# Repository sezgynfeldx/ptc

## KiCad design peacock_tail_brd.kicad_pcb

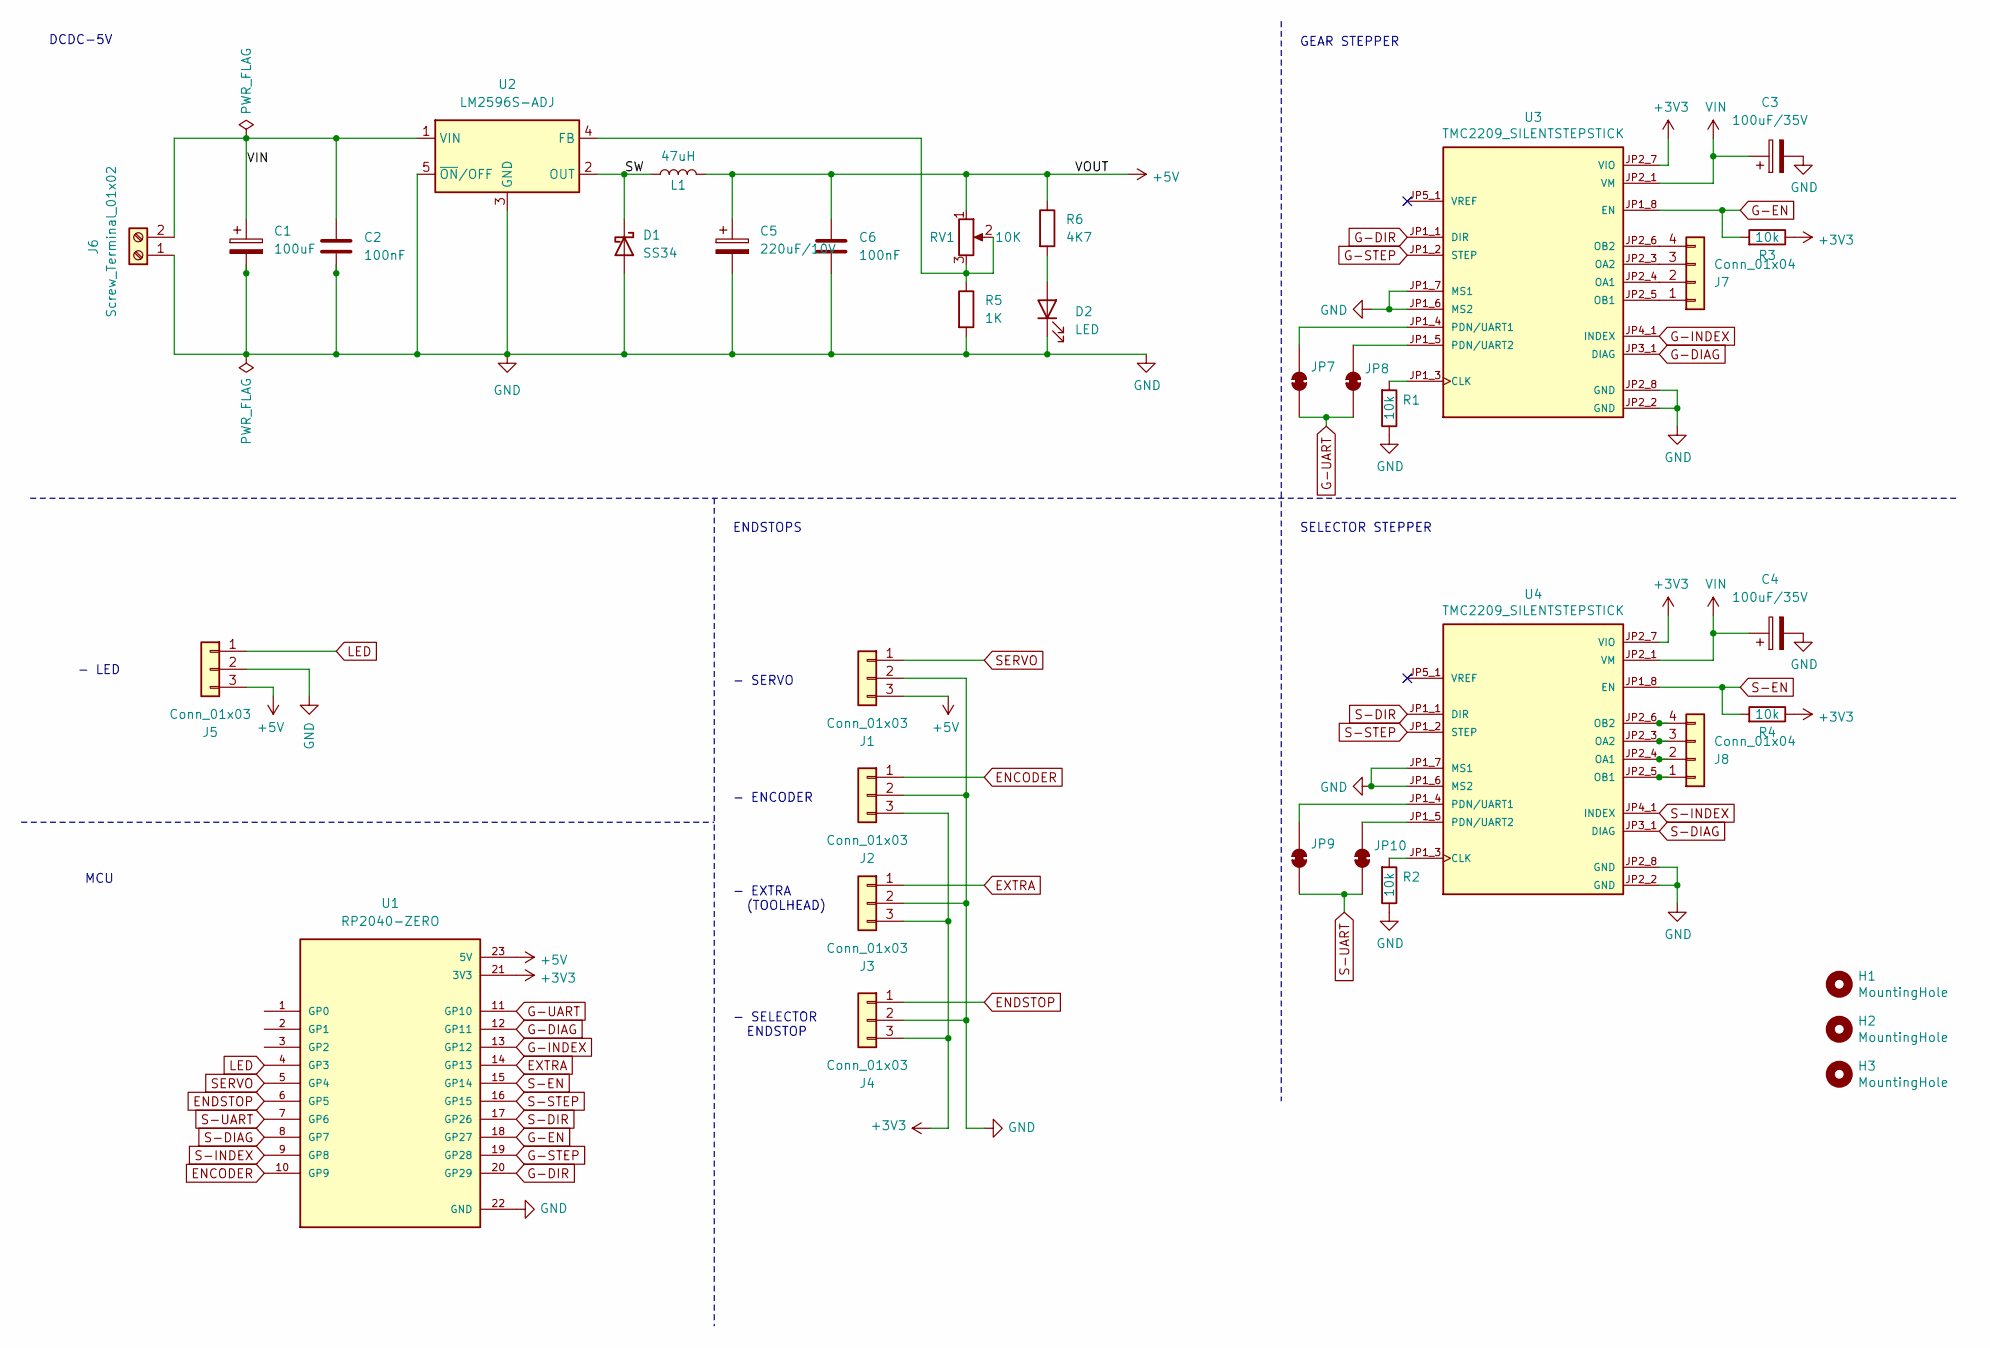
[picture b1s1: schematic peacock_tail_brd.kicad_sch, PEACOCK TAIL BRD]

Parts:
C1: 100uF; CP_Elec_6.3x7.7
C2, C6: 100nF; C_0603_1608Metric
C3, C4: 100uF/35V; CP_Elec_6.3x7.7
C5: 220uF/10V; CP_Elec_6.3x7.7
D1: SS34; D_SMA
D2: LED; LED_0603_1608Metric
H1, H2, H3: MountingHole; MountingHole_3.2mm_M3
J1, J2, J3, J4, J5: Conn_01x03; JST_XH_B3B-XH-A_1x03_P2.50mm_Vertical
J6: Screw_Terminal_01x02; TerminalBlock_bornier-2_P5.08mm_2
J7, J8: Conn_01x04; JST_XH_B4B-XH-A_1x04_P2.50mm_Vertical
JP7, JP9: SolderJumper_2_Open; SolderJumper-2_P1.3mm_Bridged_RoundedPad1.0x1.5mm
JP8, JP10: SolderJumper_2_Bridged; SolderJumper-2_P1.3mm_Bridged_RoundedPad1.0x1.5mm
L1: 47uH; L_Bourns_SRR1208_12.7x12.7mm
R1, R2, R3, R4: 10k; R_0805_2012Metric
R5: 1K; R_0603_1608Metric
R6: 4K7; R_0603_1608Metric
RV1: 10K; Potentiometer_Bourns_3296W_Vertical
U1: RP2040-ZERO; MODULE_RP2040-ZERO; PARTREV NA
U2: LM2596S-ADJ; TO-263-5_TabPin3
U3, U4: TMC2209_SILENTSTEPSTICK; MODULE_TMC2209_SILENTSTEPSTICK; PARTREV v11

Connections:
+3V3: J2.3, J3.3, J4.3, R3.2, R4.2, U1.21 (3V3), U3.JP2_7 (VIO), U4.JP2_7 (VIO)
+5V: C5.1, C6.1, J1.3, J5.3, L1.2, R6.1, RV1.1, U1.23 (5V)
/SW: D1.1 (K), L1.1, U2.2 (OUT)
ENCODER: J2.1, U1.10 (GP9)
ENDSTOP: J4.1, U1.6 (GP5)
EXTRA: J3.1, U1.14 (GP13)
G-DIAG: U1.12 (GP11), U3.JP3_1 (DIAG)
G-DIR: U1.20 (GP29), U3.JP1_1 (DIR)
G-EN: R3.1, U1.18 (GP27), U3.JP1_8 (EN)
G-INDEX: U1.13 (GP12), U3.JP4_1 (INDEX)
G-STEP: U1.19 (GP28), U3.JP1_2 (STEP)
G-UART: JP7.1 (A), JP8.2 (B), U1.11 (GP10)
GND: C1.2, C2.2, C3.2, C4.2, C5.2, C6.2, D1.2 (A), D2.1 (K), J1.2, J2.2, J3.2, J4.2, J5.2, J6.1, R1.2, R2.2, R5.2, U1.22 (GND), U2.3 (GND), U2.5 (~ON/OFF), U3.JP1_6 (MS2), U3.JP1_7 (MS1), U3.JP2_2 (GND), U3.JP2_8 (GND), U4.JP1_6 (MS2), U4.JP1_7 (MS1), U4.JP2_2 (GND), U4.JP2_8 (GND)
LED: J5.1, U1.4 (GP3)
unnamed: D2.2 (A), R6.2
unnamed: J7.1, U3.JP2_5 (OB1)
unnamed: J7.2, U3.JP2_4 (OA1)
unnamed: J7.3, U3.JP2_3 (OA2)
unnamed: J7.4, U3.JP2_6 (OB2)
unnamed: J8.1, U4.JP2_5 (OB1)
unnamed: J8.2, U4.JP2_4 (OA1)
unnamed: J8.3, U4.JP2_3 (OA2)
unnamed: J8.4, U4.JP2_6 (OB2)
unnamed: JP7.2 (B), U3.JP1_4 (PDN/UART1)
unnamed: JP8.1 (A), U3.JP1_5 (PDN/UART2)
unnamed: JP9.2 (B), U4.JP1_4 (PDN/UART1)
unnamed: JP10.1 (A), U4.JP1_5 (PDN/UART2)
unnamed: R5.1, RV1.2, RV1.3, U2.4 (FB)
unnamed: R1.1, U3.JP1_3 (CLK)
unnamed: R2.1, U4.JP1_3 (CLK)
S-DIAG: U1.8 (GP7), U4.JP3_1 (DIAG)
S-DIR: U1.17 (GP26), U4.JP1_1 (DIR)
S-EN: R4.1, U1.15 (GP14), U4.JP1_8 (EN)
S-INDEX: U1.9 (GP8), U4.JP4_1 (INDEX)
S-STEP: U1.16 (GP15), U4.JP1_2 (STEP)
S-UART: JP9.1 (A), JP10.2 (B), U1.7 (GP6)
SERVO: J1.1, U1.5 (GP4)
VIN: C1.1, C2.1, C3.1, C4.1, J6.2, U2.1 (VIN), U3.JP2_1 (VM), U4.JP2_1 (VM)

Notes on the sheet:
GEAR STEPPER
- EXTRA (TOOLHEAD)
SELECTOR STEPPER
- SELECTOR ENDSTOP
ENDSTOPS
- SERVO
- LED
MCU
- ENCODER
DCDC-5V

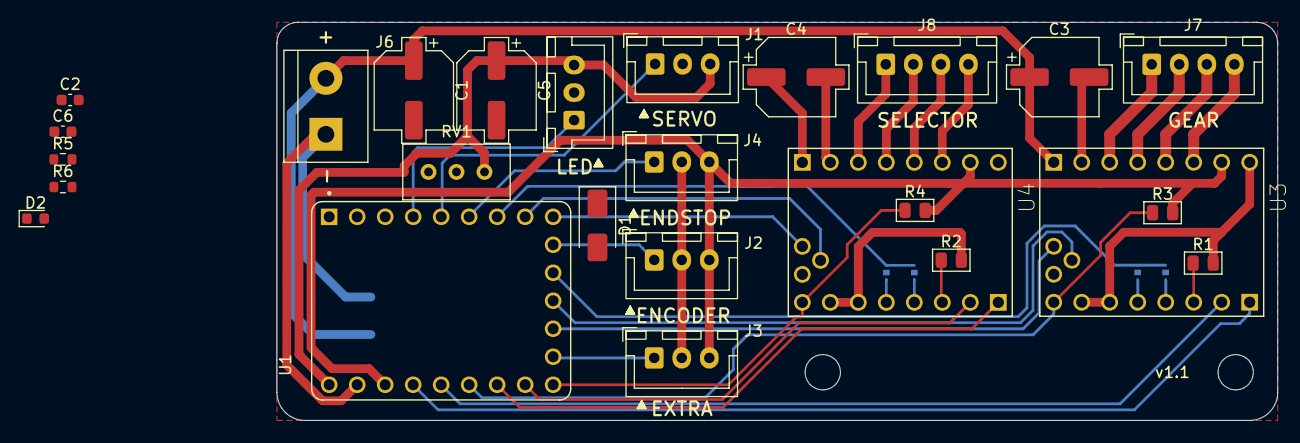
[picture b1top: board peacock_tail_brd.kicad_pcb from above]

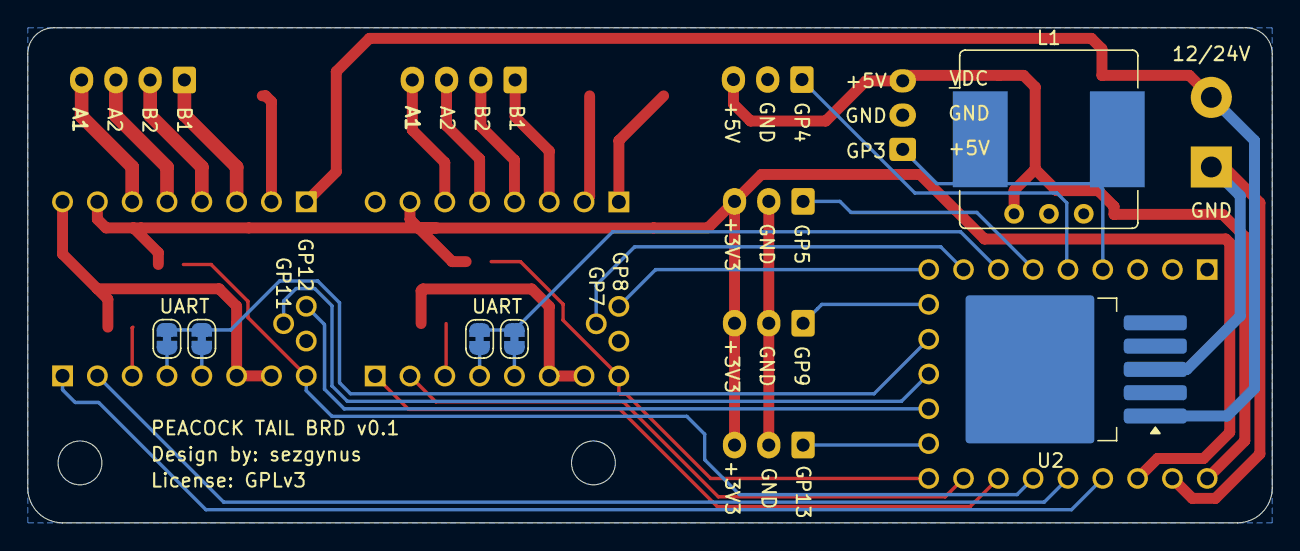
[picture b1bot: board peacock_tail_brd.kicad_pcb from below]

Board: 2 copper layers, 90.8 x 36.1 mm, 35 parts (6 on the bottom side), 38 nets.

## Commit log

2026-04-29 3d model alignment
2026-04-29 connected missing nets
2026-04-30 lm2596 update

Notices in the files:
peacock_tail_brd.kicad_pcb:
License: GPLv3
